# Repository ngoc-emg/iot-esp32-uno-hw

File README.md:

# iot-esp32-uno-hw

## Features

- Power input 4V to 30V and 5V USB.
- Auto enter program mode via Serial - Pre-program OTA firmware.
- ESP32 and Arduino Library.
- Vietnamese doc support from [https://esp8266.vn](https://esp8266.vn).
- Open hardware with CC-BY-SA license.
- Design with KiCad.

## Hardware.

- Microcontroller: ESP-32 WROVER.
	- CPU: ESP-32.
	- Architecture: 32-bit with TSMC ultra-low power 40nm technology.
- Operating Voltage: 3.3V.
- IO Voltage: 3.3V.
- IO pin: 23 pin with 6 pin Analog (A0-A5).
- Support display with header oled.
- 1 reset button, 1 flash button.

### Schematic.

<<<<<<< HEAD

### 3D

=======

### 3D
>>>>>>> esp/master

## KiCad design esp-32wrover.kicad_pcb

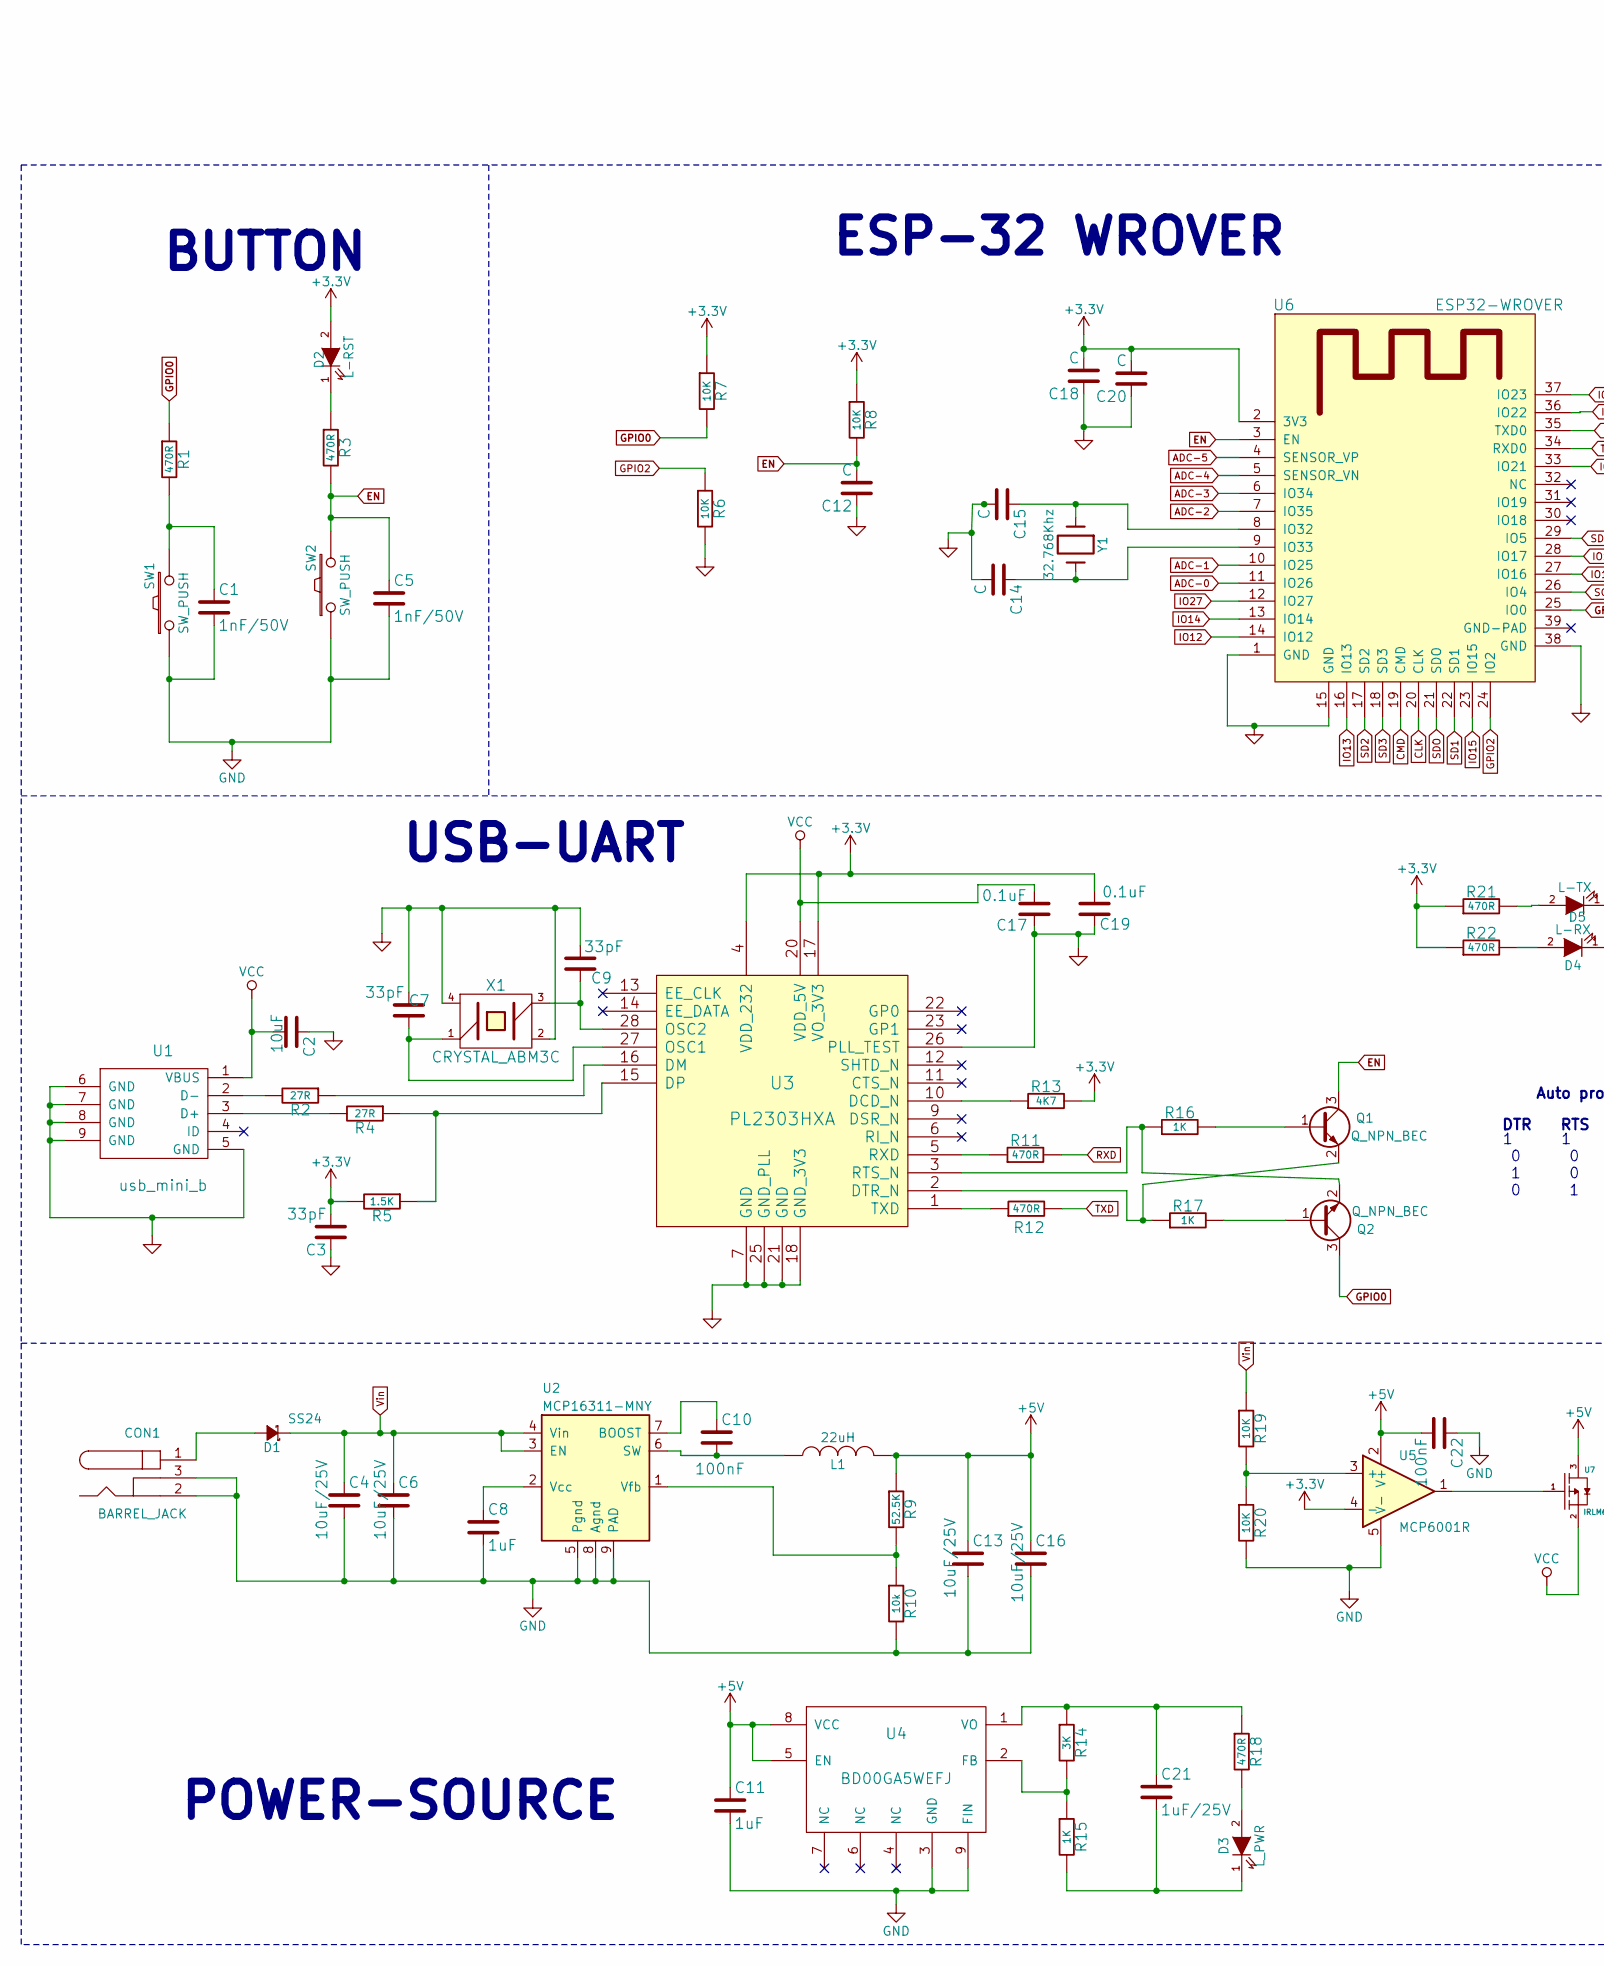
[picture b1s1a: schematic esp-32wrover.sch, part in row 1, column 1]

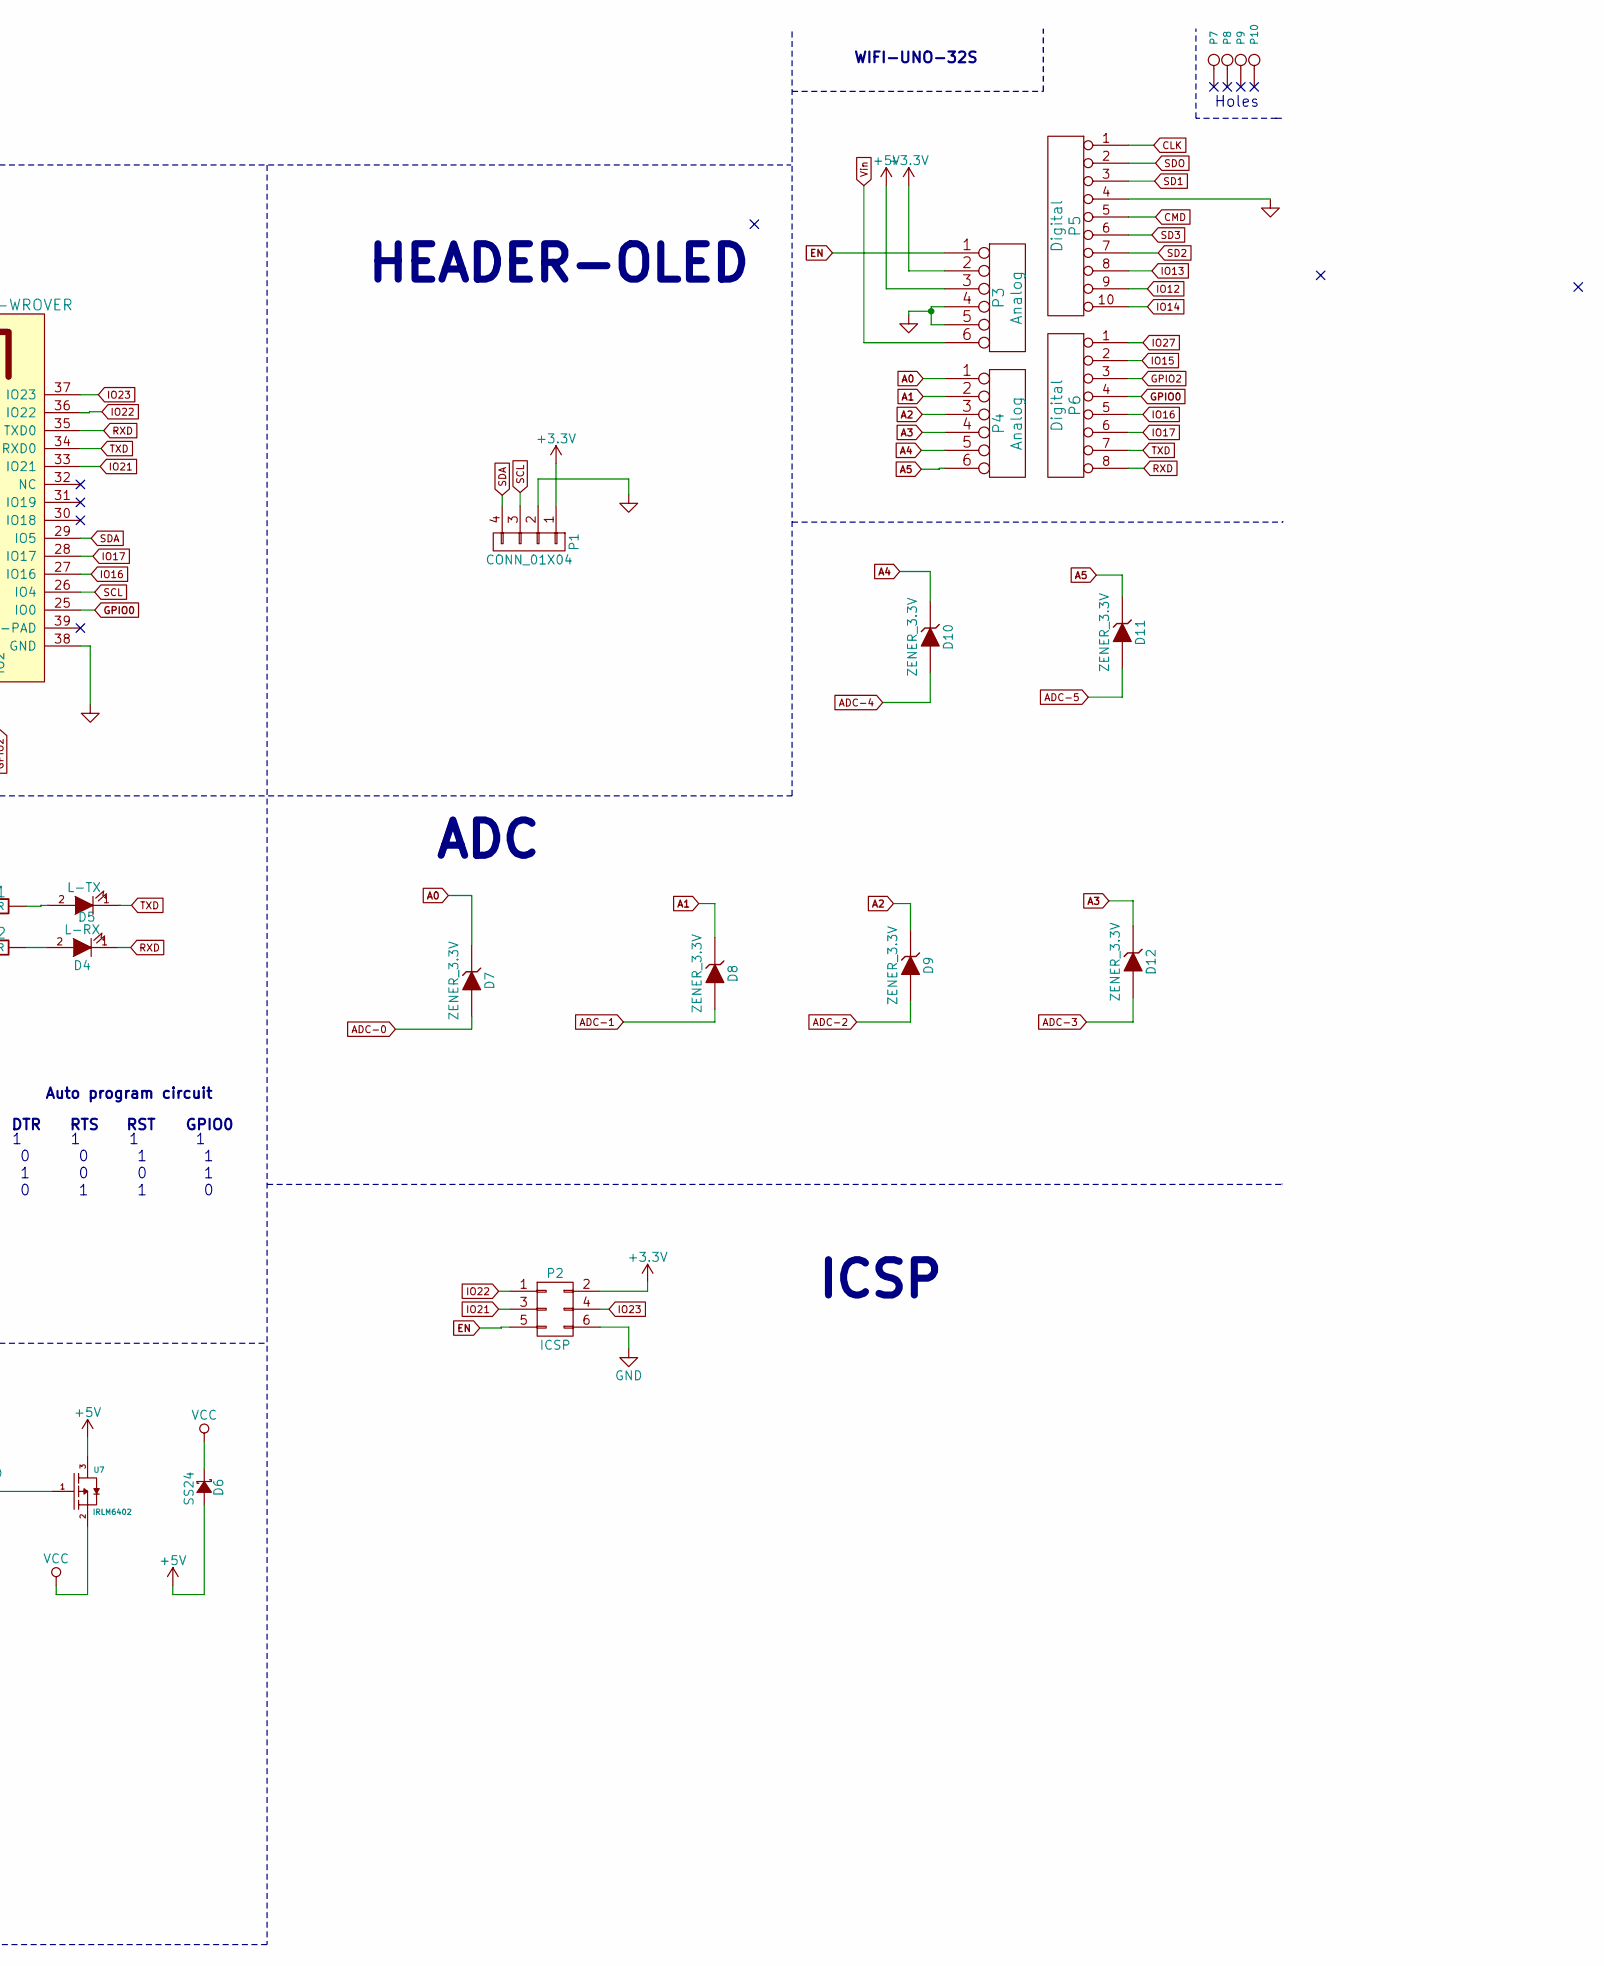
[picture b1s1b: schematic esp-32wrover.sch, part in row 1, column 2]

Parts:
C1, C5: 1nF/50V; C_0603
C2: 10uF; C_0603
C3, C7, C9: 33pF; C_0603
C4, C6: 10uF/25V; C_1210
C8: 1uF; C_0603
C10: 100nF; C_0603
C11: 1uF; C_0805
C12, C14, C15: C; C_0603
C13, C16: 10uF/25V; C_0603
C17, C19: 0.1uF; C_0603
C18, C20: C; C_0805
C21: 1uF/25V; C_0603
C22: 100nF; C_0805
CON1: BARREL_JACK; JACK_ALIM
D1, D6: SS24; D_0805
D2: L-RST; LED_0603
D3: L_PWR; LED_0603
D4: L-RX; LED_0603
D5: L-TX; LED_0603
D7, D8, D9, D10, D11, D12: ZENER_3.3V; D_0603
L1: 22uH; SELF-WE-TPC_M
P1: CONN_01X04; Pin_Header_Straight_1x04_Pitch2.54mm
P2: ICSP; Pin_Header_Straight_2x03_Pitch2.54mm
P3, P4: Analog; Socket_Strip_Arduino_1x06
P5: Digital; Socket_Strip_Arduino_1x10
P6: Digital; Socket_Strip_Arduino_1x08
P7, P8, P9, P10: CONN_1; Arduino_1pin
Q1, Q2: Q_NPN_BEC; SOT-23
R1, R3, R11, R12, R18, R21, R22: 470R; R_0603
R2, R4: 27R; R_0603
R5: 1.5K; R_0603
R6, R7, R8, R19, R20: 10K; R_0603
R9: 52.5K; R_0603
R10: 10k; R_0603
R13: 4K7; R_0603
R14: 3K; R_0603
R15, R16, R17: 1K; R_0603
SW1, SW2: SW_PUSH; SW_SPST_EVQPE1
U1: usb_mini_b; USB_Mini-B
U2: MCP16311-MNY; MSOP-8-1EP_3x3mm_Pitch0.65mm
U3: PL2303HXA; SSOP-28_5.3x10.2mm_Pitch0.65mm
U4: BD00GA5WEFJ; MSOP-8-1EP_3x3mm_Pitch0.65mm
U5: MCP6001R; SOT-23-5
U6: ESP32-WROVER; esp32-wrover
U7: IRLM6402; SOT-23
X1: CRYSTAL_ABM3C; Crystal_SMD_5032-4pin_5.0x3.2mm
Y1: 32.768Khz; Crystal_DS26_d2.0mm_l6.0mm_Horizontal

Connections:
+3V3: C3.2, C18.2, C19.2, C20.2, D2.2 (A), P1.1, P2.2, P3.2, R5.2, R7.1, R8.1, R13.2, R21.1, R22.1, U3.4 (VDD_232), U3.17 (VO_3V3), U5.4 (-), U6.2 (3V3)
+5V: C11.1, C13.1, C16.1, C22.2, D6.2 (A), L1.2, P3.3, R9.1, U4.5 (EN), U4.8 (VCC), U5.2 (V+), U7.3
A0: D7.1 (K), P4.1
A1: D8.1 (K), P4.2
A2: D9.1 (K), P4.3
A3: D12.1 (K), P4.4
A4: D10.1 (K), P4.5
A5: D11.1 (K), P4.6
ADC-0: D7.2 (A), U6.11 (IO26)
ADC-1: D8.2 (A), U6.10 (IO25)
ADC-2: D9.2 (A), U6.7 (IO35)
ADC-3: D12.2 (A), U6.6 (IO34)
ADC-4: D10.2 (A), U6.5 (SENSOR_VN)
ADC-5: D11.2 (A), U6.4 (SENSOR_VP)
CLK: P5.1, U6.20 (CLK)
CMD: P5.5, U6.19 (CMD)
EN: C5.1, C12.2, P2.5, P3.1, Q1.3 (C), R3.2, R8.2, SW2.2, U6.3 (EN)
GND: C1.2, C2.1, C3.1, C4.2, C5.2, C6.2, C7.2, C8.2, C9.2, C11.2, C12.1, C13.2, C14.2, C15.2, C16.2, C17.1, C18.1, C19.1, C20.1, C22.1, CON1.2, CON1.3, P1.2, P2.6, P3.4, P3.5, P5.4, R6.2, R10.2, R20.2, SW1.1, SW2.1, U1.5 (GND), U1.6 (GND), U1.7 (GND), U1.8 (GND), U1.9 (GND), U2.5 (Pgnd), U2.8 (Agnd), U2.9 (PAD), U3.7 (GND), U3.18 (GND_3V3), U3.21 (GND), U3.25 (GND_PLL), U3.26 (PLL_TEST), U4.3 (GND), U4.9 (FIN), U5.5 (V-), U6.1 (GND), U6.15 (GND), U6.38 (GND), X1.2 (GND), X1.4 (GND)
GPIO0: P6.4, Q2.3 (C), R1.1, R7.2, U6.25 (IO0)
GPIO2: P6.3, R6.1, U6.24 (IO2)
IO12: P5.9, U6.14 (IO12)
IO13: P5.8, U6.16 (IO13)
IO14: P5.10, U6.13 (IO14)
IO15: P6.2, U6.23 (IO15)
IO16: P6.5, U6.27 (IO16)
IO17: P6.6, U6.28 (IO17)
IO21: P2.3, U6.33 (IO21)
IO22: P2.1, U6.36 (IO22)
IO23: P2.4, U6.37 (IO23)
IO27: P6.1, U6.12 (IO27)
unnamed: C1.1, R1.2, SW1.2
unnamed: C7.1, U3.27 (OSC1), X1.1
unnamed: C8.1, U2.2 (Vcc)
unnamed: C9.1, U3.28 (OSC2), X1.3
unnamed: C10.1, U2.7 (BOOST)
unnamed: C10.2, L1.1, U2.6 (SW)
unnamed: C14.1, U6.9 (IO33), Y1.2
unnamed: C15.1, U6.8 (IO32), Y1.1
unnamed: C21.1, R14.1, R18.1, U4.1 (VO)
unnamed: C21.2, D3.1 (K), R15.2
unnamed: CON1.1, D1.2 (A)
unnamed: D2.1 (K), R3.1
unnamed: D3.2 (A), R18.2
unnamed: D4.2 (A), R22.2
unnamed: D5.2 (A), R21.2
unnamed: Q1.1 (B), R16.2
unnamed: Q1.2 (E), R17.1, U3.2 (DTR_N)
unnamed: Q2.1 (B), R17.2
unnamed: Q2.2 (E), R16.1, U3.3 (RTS_N)
unnamed: R2.1, U3.16 (DM)
unnamed: R2.2, U1.2 (D-)
unnamed: R4.1, R5.1, U3.15 (DP)
unnamed: R4.2, U1.3 (D+)
unnamed: R9.2, R10.1, U2.1 (Vfb)
unnamed: R11.1, U3.5 (RXD)
unnamed: R12.1, U3.1 (TXD)
unnamed: R13.1, U3.10 (DCD_N)
unnamed: R14.2, R15.1, U4.2 (FB)
unnamed: R19.2, R20.1, U5.3 (+)
unnamed: U5.1, U7.1
RXD: D4.1 (K), P6.8, R11.2, U6.35 (TXD0)
SCL: P1.3, U6.26 (IO4)
SD1: P5.3, U6.22 (SD1)
SD2: P5.7, U6.17 (SD2)
SD3: P5.6, U6.18 (SD3)
SDA: P1.4, U6.29 (IO5)
SDO: P5.2, U6.21 (SDO)
TXD: D5.1 (K), P6.7, R12.2, U6.34 (RXD0)
VCC: C2.2, C17.2, D6.1 (K), U1.1 (VBUS), U3.20 (VDD_5V), U7.2
Vin: C4.1, C6.1, D1.1 (K), P3.6, R19.1, U2.3 (EN), U2.4 (Vin)

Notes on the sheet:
Holes
WIFI-UNO-32S
POWER-SOURCE
USB-UART
BUTTON
HEADER-OLED
1 1 1 1 0 0 1 1 1 0 0 1 0 1 1 0
Auto program circuit
DTR
RTS
RST
GPIO0
ADC
ESP-32 WROVER
ICSP

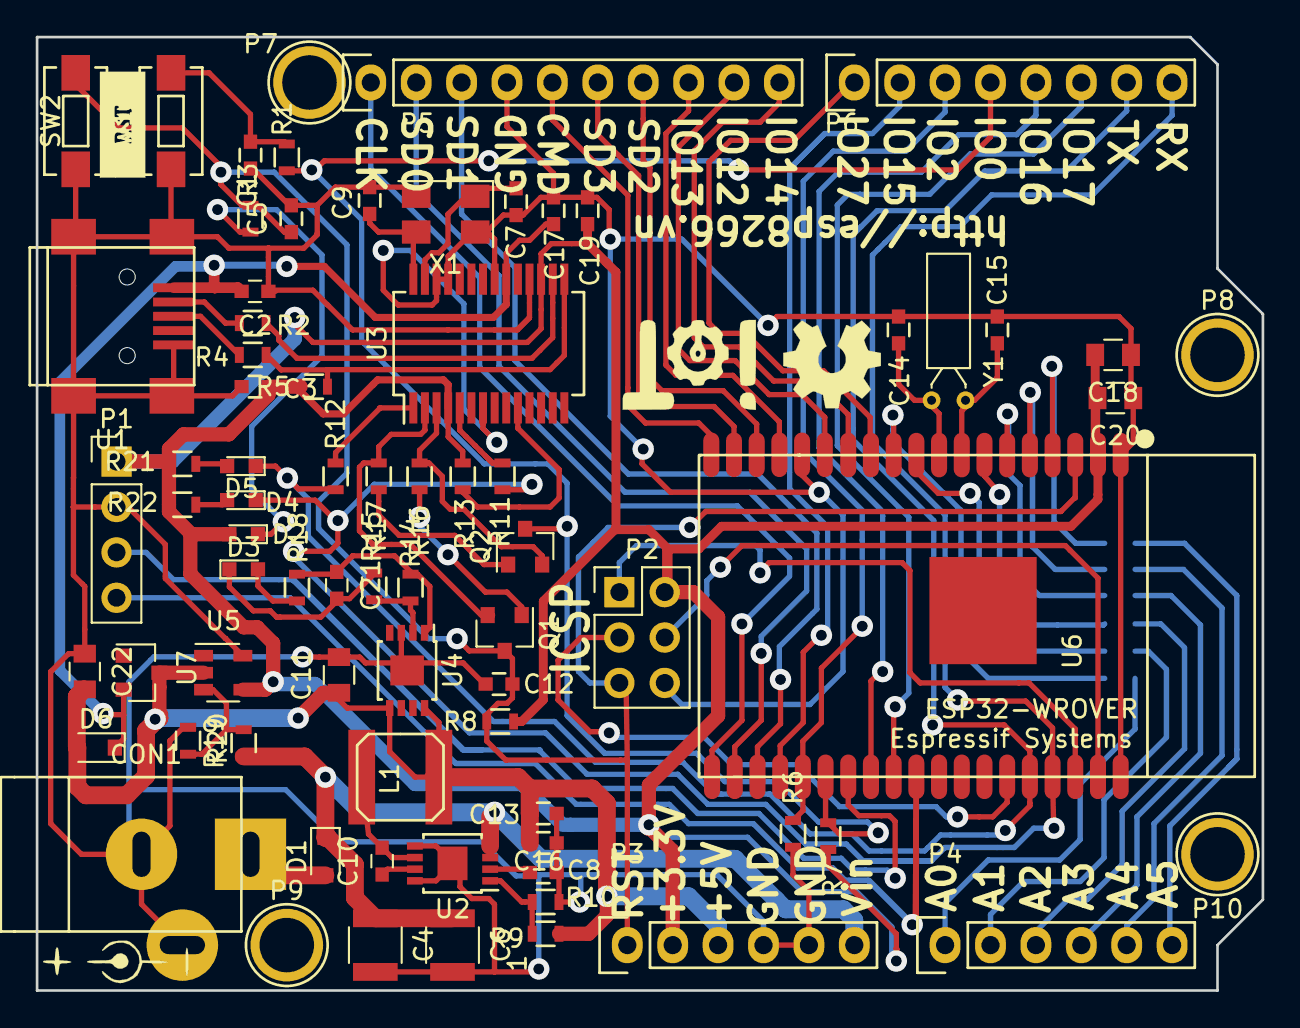
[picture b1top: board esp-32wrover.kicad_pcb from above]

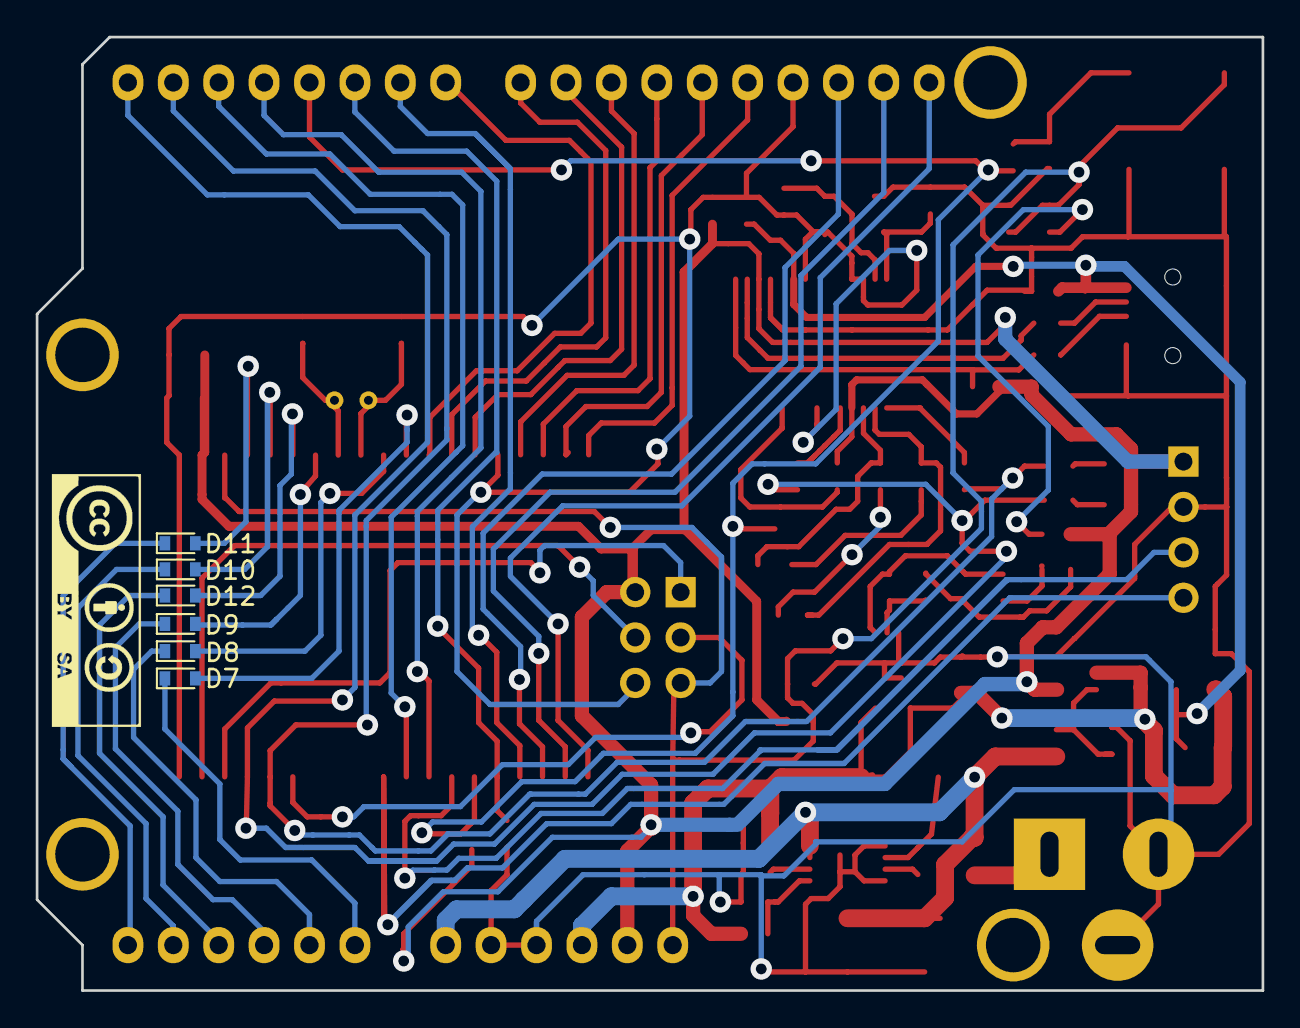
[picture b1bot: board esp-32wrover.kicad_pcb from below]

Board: 2 copper layers, 68.6 x 53.3 mm, 81 parts (6 on the bottom side), 70 nets.

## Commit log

2017-01-05 bắt đầu vẽ mạch nguyên lý
2017-01-05 cap nhat .gitignore
2017-01-05 xoa file
2017-01-05 tạo khối usb
2017-01-06 tạo khối ADC
2017-01-06 edit file readme.md
2017-01-06 add esp-block-dia-gram
2017-01-06 them hardware
2017-01-06 nối IO
2017-01-06 noi io
2017-01-06 them noconnect
2017-01-07 add netlist
2017-01-07 edit netlist, create pcb
2017-01-07 edit .gitignore
2017-01-07 edit .ignore
2017-01-09 thêm header ICSP
2017-01-09 xóa hello.c
2017-01-10 sap xep linh kien
2017-01-11 đi dây PCB
2017-01-11 sủa lỗi kích thước via
2017-01-11 xoá file autosave
2017-01-11 điều chỉnh độ rộng đường đi dây theo đúng quy cách
2017-01-11 sửa thư viện chân cho esp32-wrover
2017-01-16 sắp xếp linh kiện, đi dây
2017-01-16 thêm thư viện 3d cho esp32
2017-01-17 edit esp-3d
2017-01-18 edit readme
2017-01-19 cap nhat 3d cho pcb
